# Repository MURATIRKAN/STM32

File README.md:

YAZILIM GELİŞTİRME ORTAMI STMCUBE IDE VEYA KEIL ARM : 2021-2024 
STM32 ARM GELİŞTİRME KART SERİSİ
MODEL KARTLAR: E-H
TASARIM:
TASARIM PROGRAMI:AUTODESK EAGLE
DIPTRACE FREE VERSİYON.
----------------------------------

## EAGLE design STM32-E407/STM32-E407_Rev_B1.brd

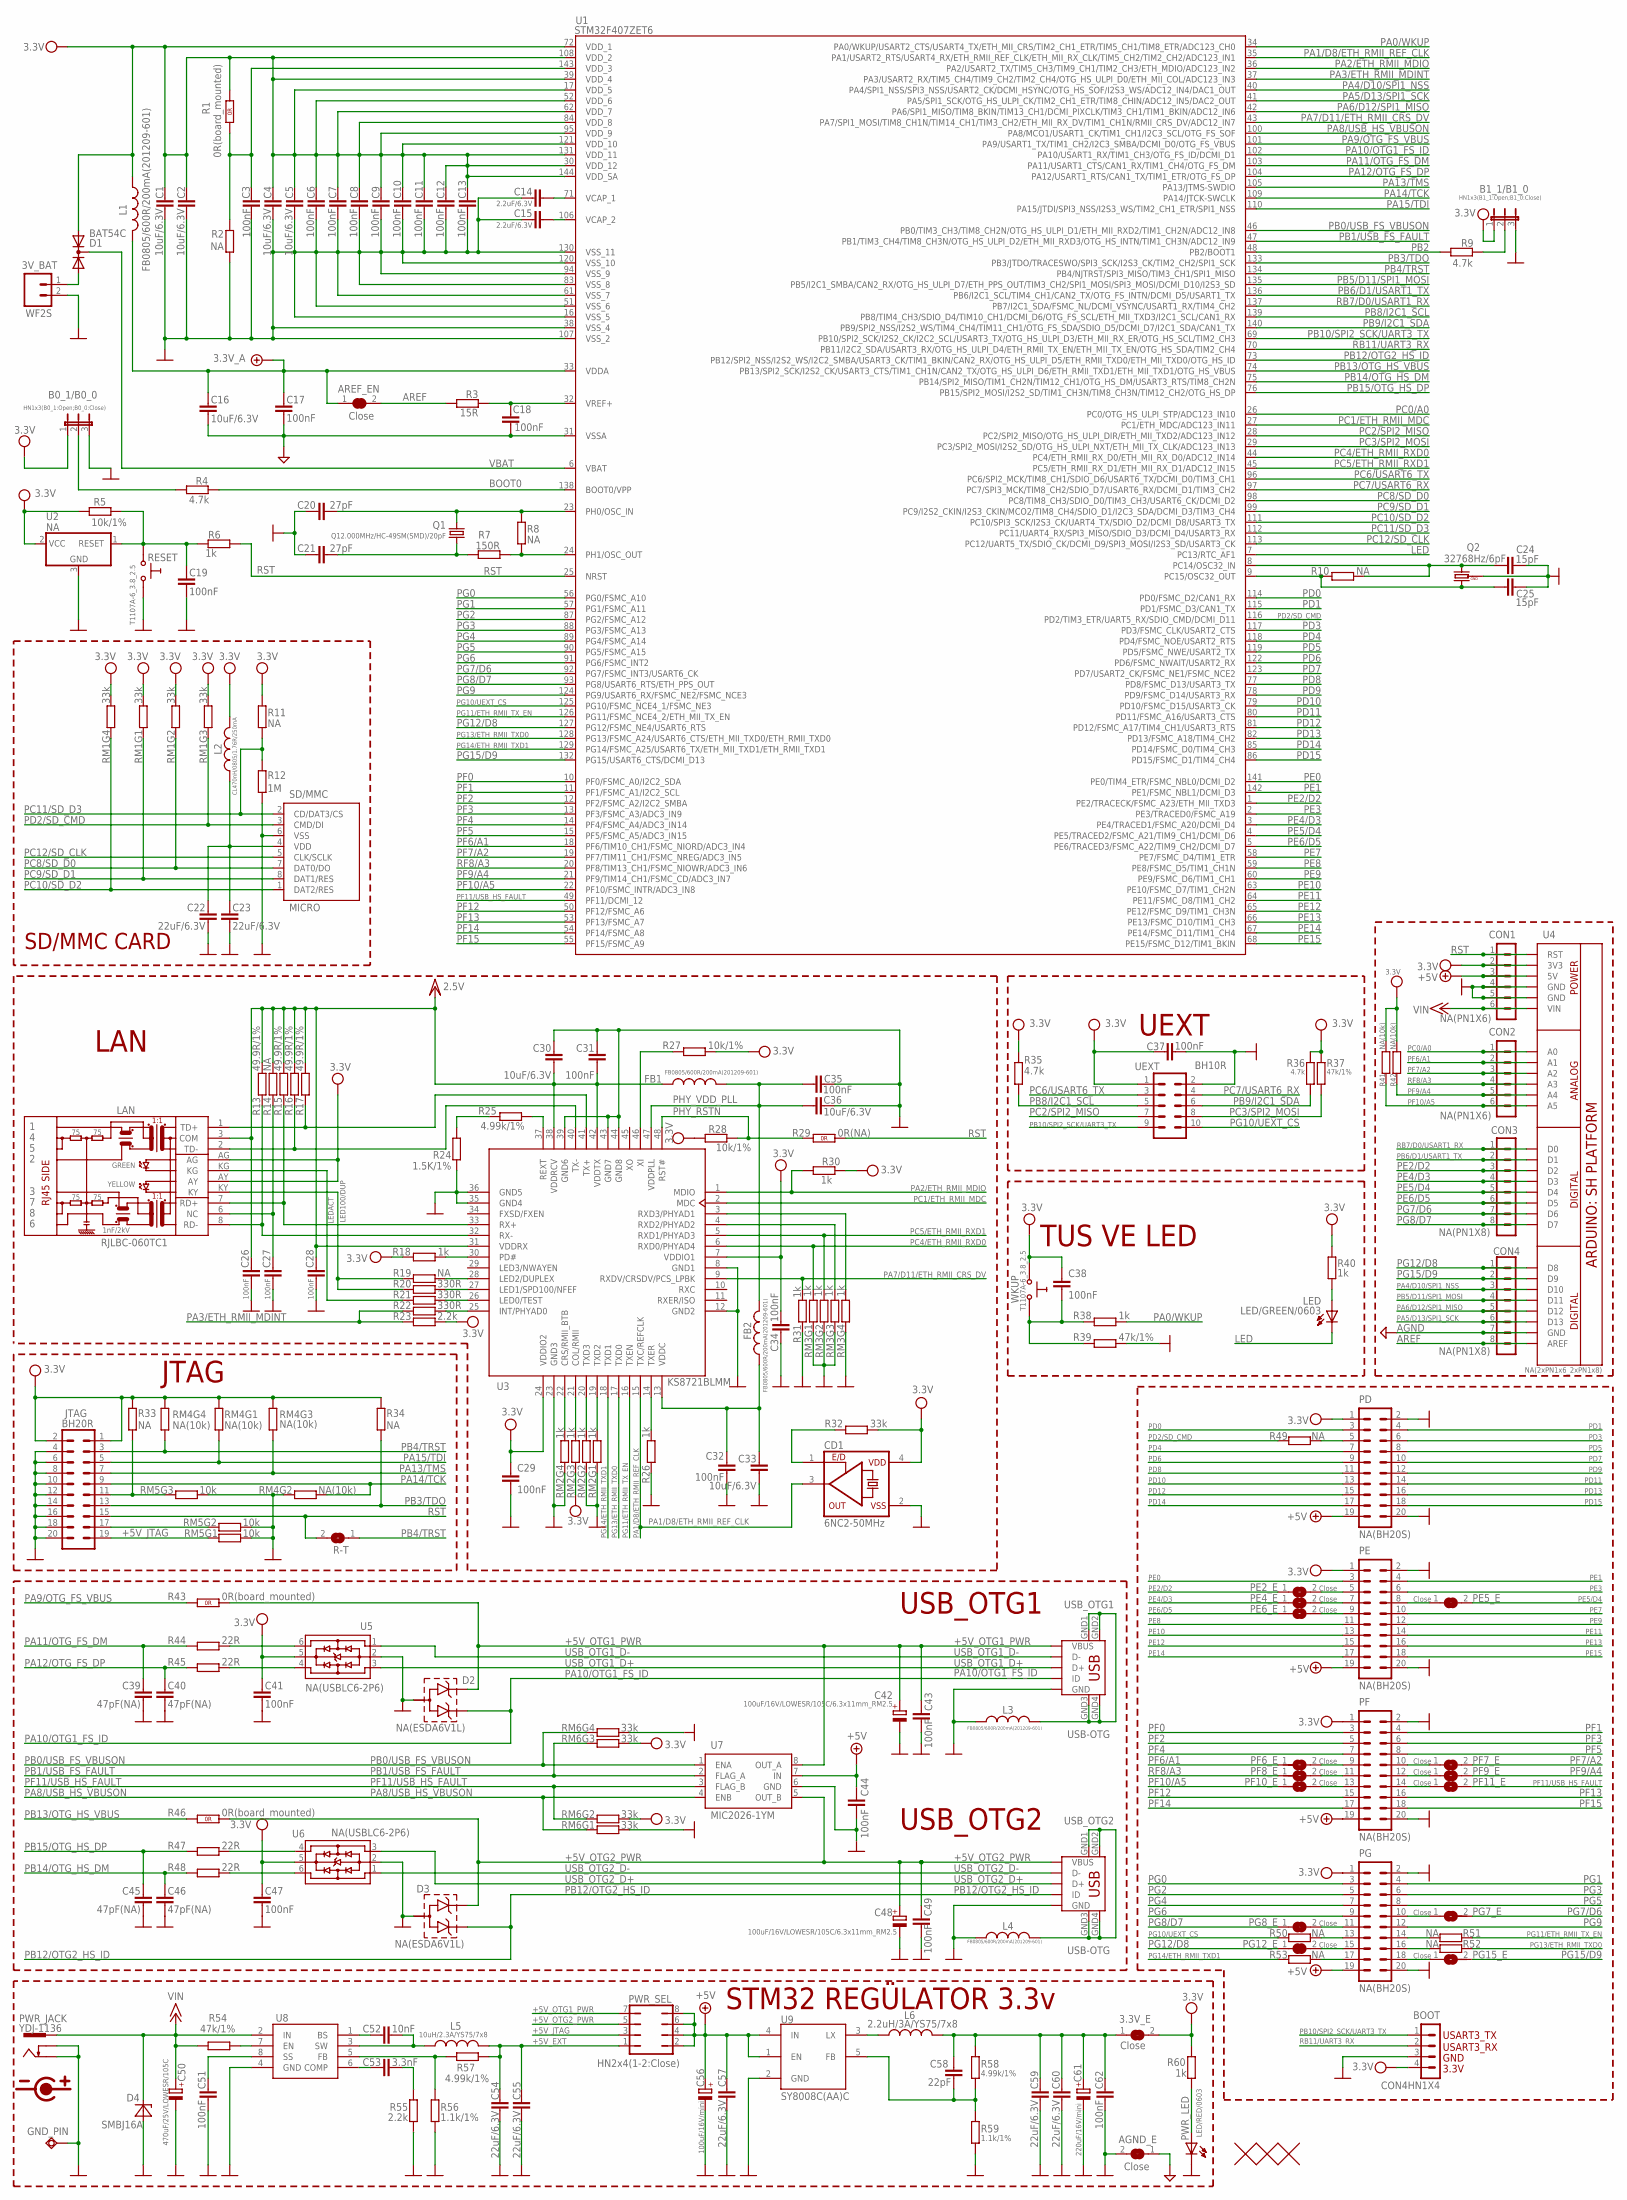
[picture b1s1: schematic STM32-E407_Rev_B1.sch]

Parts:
3.3V_E: Close; SJ_1_SMALLER_CLOSE
3V_BAT: WF2S; CON2.54MM-2-0
AGND_E: Close; SJ_1_SMALLER_CLOSE
AREF_EN: Close; SJ_1_SMALLER_CLOSE
B0_1/B0_0: HN1x3(B0_1:Open;B0_0:Close); JP2
B1_1/B1_0: HN1x3(B1_1:Open;B1_0:Close); JP2
BOOT: CON4HN1X4; HN1X4
C1, C2, C4, C5, C16, C30, C33, C36: 10uF/6.3V; C0603_DWS
C3, C6, C7, C8, C9, C10, C11, C12, C13, C17, C18, C19, C26, C27, C28, C29, C31, C32, C34, C35, C37, C38, C41, C43, C44, C47, C49, C51, C62: 100nF; C0603_DWS
C14, C15: 2.2uF/6.3V; C0603_DWS
C20, C21: 27pF; C0603_DWS
C22, C23, C54, C55, C57, C59, C60: 22uF/6.3V; C0603_DWS
C24, C25: 15pF; C0603_DWS
C39, C40, C45, C46: 47pF(NA); C0603_DWS
C42, C48: 100uF/16V/LOWESR/105C/6.3x11mm_RM2.5; E2,5-6,3
C50: 470uF/25V/LOWESR/105C; E5-10,5
C52: 10nF; C0603_DWS
C53: 3.3nF; C0603_DWS
C56: 100uF/16V/mini; E2,5-6
C58: 22pF; C0603_DWS
C61: 220uF/16V/mini; E3,5-8
CD1: 6NC2-50MHz; 7X5MM_CLOCK_DRIVER
CON1, CON2: NA(PN1X6); PN1X6
CON3, CON4: NA(PN1X8); PN1X8
D1: BAT54C; SOT23C
D2, D3: NA(ESDA6V1L); SOT-23
D4: SMBJ16A; DO214AA
FB1, FB2: FB0805/600R/200mA(201209-601); L0805_5MIL_DWS
GND_PIN: TESTPAD3; TEST_PAD40/70/SQUARE
JTAG: BH20R
L1, L3, L4: FB0805/600R/200mA(201209-601); L0805_5MIL_DWS
L2: CL470nH/0805/1.76R/250mA; L0805_5MIL_DWS
L5: 10uH/2.3A/YS75/7x8; L7078
L6: 2.2uH/3A/YS75/7x8; L7078
LAN: RJLBC-060TC1
LED: LED/GREEN/0603; LED-0603
PD: NA(BH20S); ML20-MALE
PE: NA(BH20S); ML20-MALE
PE2_E, PE4_E, PE5_E, PE6_E: Close; SJ_1_SMALLER_CLOSE
PF: NA(BH20S); ML20-MALE
PF6_E, PF7_E, PF8_E, PF9_E, PF10_E, PF11_E: Close; SJ_1_SMALLER_CLOSE
PG: NA(BH20S); ML20-MALE
PG7_E, PG8_E, PG12_E, PG15_E: Close; SJ_1_SMALLER_CLOSE
PWR_JACK: YDJ-1136; PWR_JACK_UNI_MILLING
PWR_LED: LED/RED/0603; LED-0603
PWR_SEL: HN2x4(1-2:Close); JP4Q_2
Q1: Q12.000MHz/HC-49SM(SMD)/20pF; HC49/SMD2_THIN
Q2: 32768Hz/6pF; TC26H_3_REPAIR_SMD
R1, R43, R46: 0R(board_mounted); 0603_0R
R2, R8, R10, R11, R14, R19, R33, R34: NA; R0603_5MIL_DWS_NA
R3: 15R; R0603_5MIL_DWS
R4, R9, R35, R36: 4.7k; R0603_5MIL_DWS
R5, R27, R28: 10k/1%; R0603_5MIL_DWS
R6, R18, R26, R30, R31, R38, R40, R60: 1k; R0603_5MIL_DWS
R7: 150R; R0603_5MIL_DWS
R12: 1M; R0603_5MIL_DWS
R13, R15, R16, R17: 49.9R/1%; R0603_5MIL_DWS
R20, R21, R22: 330R; R0603_5MIL_DWS
R23, R55: 2.2k; R0603_5MIL_DWS
R24: 1.5K/1%; R0603_5MIL_DWS
R25, R57, R58: 4.99k/1%; R0603_5MIL_DWS
R29: 0R(NA); 0603_0R
R32: 33k; R0603_5MIL_DWS
R37, R39, R54: 47k/1%; R0603_5MIL_DWS
R41, R42: NA(10k); R0603_5MIL_DWS_NA
R44, R45, R47, R48: 22R; R0603_5MIL_DWS
R49, R50, R51, R52, R53: NA; R0603_5MIL_DWS
R56, R59: 1.1k/1%; R0603_5MIL_DWS
R-T: Open; SJ_1_SMALLER
RESET: T1107A-6_3.8_2.5; SW-TAKT_6X3.5_SMD
RM1, RM6: 33k; R_MATRIX_4
RM2, RM3: 1k; R_MATRIX_4
RM4: NA(10k); R_MATRIX_4
RM5: 10k; R_MATRIX_4
SD/MMC: MICRO; TFR-MEM-CON
U1: STM32F407ZET6; LQFP144
U2: NA; SOT23
U3: KS8721BLMM; LQFP48_MM
U4: NA(2xPN1x6_2xPN1x8); ARDUINO_SHIELD_PLATFORM_WITHOUT_DIMENSION
U5, U6: NA(USBLC6-2P6); USBLC6-2P6
U7: MIC2026-1YM; SO-8
U8: MP1482DS; SOIC8
U9: SY8008C(AA)C; SOT23-5
U$1, U$2, U$9: FIDUCIAL1X2; FIDUCIAL-1X2
UEXT: BH10R
USB_OTG1, USB_OTG2: USB-OTG; USB_MINI_9PIN
WKUP: T1107A-6_3.8_2.5; SW-TAKT_6X3.5_SMD

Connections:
+5V: C44.1, C56.+, C57.1, CON1.3, PD.19, PE.19, PF.19, PG.19, PWR_SEL.2, PWR_SEL.4, PWR_SEL.6, PWR_SEL.8, U4.5V, U7.7 (IN), U9.1 (EN), U9.4 (IN)
+5V_EXT: C54.1, C55.1, L5.2, PWR_SEL.1, R57.2
+5V_JTAG: JTAG.19, PWR_SEL.3, RM5.1.1 (1)
+5V_OTG1_PWR: C42.+, C43.1, D2.1, PWR_SEL.7, R43.2 (1.2), U7.8 (OUT_A), USB_OTG1.VBUS
+5V_OTG2_PWR: C48.+, C49.1, D3.1, PWR_SEL.5, R46.2 (1.2), U7.5 (OUT_B), USB_OTG2.VBUS
+7V: AREF_EN.1, C16.1, C17.2, L1.2, U1.33 (VDDA)
+15V: C50.+, CON1.6, D4.C, PWR_JACK.+, R54.1, U4.VIN, U8.2 (IN)
AGND: AGND_E.1, C16.2, C17.1, C18.1, CON4.7, U1.31 (VSSA), U4.GND@2 (GND)
AREF: AREF_EN.2, CON4.8, R3.1, U4.AREF
BOOT0: R4.1, U1.138 (BOOT0/VPP)
GND: 3V_BAT.2, AGND_E.2, B0_1/B0_0.3, B1_1/B1_0.3, BOOT.3, C1.1, C2.1, C3.1, C4.1, C5.1, C6.1, C7.1, C8.1, C9.1, C10.1, C11.1, C12.1, C13.1, C14.1, C15.1, C19.1, C20.2, C21.2, C22.2, C23.2, C24.2, C25.2, C26.2, C27.1, C28.2, C29.2, C30.1, C31.1, C32.2, C33.2, C34.2, C35.2, C36.2, C37.1, C39.2, C40.2, C41.1, C42.-, C43.2, C44.2, C45.2, C46.2, C47.1, C48.-, C49.2, C50.-, C51.2, C54.2, C55.2, C56.-, C57.2, C59.2, C60.2, C61.-, C62.2, CD1.2 (VSS), CON1.4, CON1.5, D2.3, D3.3, D4.A, GND_PIN.P$1, JTAG.4, JTAG.6, JTAG.8, JTAG.10, JTAG.12, JTAG.14, JTAG.16, JTAG.18, JTAG.20, L3.1, L4.1, PD.2, PD.20, PE.2, PE.20, PF.2, PF.20, PG.2, PG.20, PWR_JACK.-, PWR_JACK.--, PWR_LED.C, Q2.GND, R2.2, R12.2, R24.2, R26.2, R31.2, R39.1, R55.2, R56.2, R59.2, RESET.P$2 (1), RM2.1.1 (1), RM2.2.1 (1), RM2.4.1 (1), RM3.1.2 (2), RM3.2.2 (2), RM3.3.2 (2), RM3.4.2 (2), RM4.2.1 (1), RM5.1.2 (2), RM5.2.2 (2), RM5.3.2 (2), RM6.1.2 (2), RM6.4.2 (2), SD/MMC.6 (VSS), U1.16 (VSS_5), U1.38 (VSS_4), U1.51 (VSS_6), U1.61 (VSS_7), U1.83 (VSS_8), U1.94 (VSS_9), U1.107 (VSS_2), U1.120 (VSS_10), U1.130 (VSS_11), U2.3 (GND), U3.8 (GND1), U3.12 (GND2), U3.23 (GND3), U3.35 (GND4), U3.36 (GND5), U3.39 (GND6), U3.43 (GND7), U3.44 (GND8), U4.GND, U4.GND@1 (GND), U5.2, U6.2, U7.6 (GND), U8.4 (GND), U9.2 (GND), UEXT.2, USB_OTG1.GND, USB_OTG2.GND
LED: LED.C, U1.7 (PC13/RTC_AF1)
LED100/DUP: LAN.KY, R19.1, R20.1
LEDACT: LAN.KG, R21.1
unnamed: C20.1, Q1.2, R8.2, U1.23 (PH0/OSC_IN)
unnamed: C21.1, Q1.1, R7.1
unnamed: R7.2, R8.1, U1.24 (PH1/OSC_OUT)
unnamed: JTAG.17, RM5.2.1 (1)
unnamed: LED.A, R40.1
unnamed: PD.5, R49.1
unnamed: R24.1, R25.1
unnamed: C58.2, R58.2, R59.1, U9.5 (FB)
unnamed: B0_1/B0_0.2, R4.2
unnamed: 3.3V_E.1, C58.1, C59.1, C60.1, C61.+, C62.1, L6.2, R58.1
unnamed: C32.1, C33.1, FB2.2, U3.13 (VDDC)
unnamed: PG.14, R51.2
unnamed: PF.13, PF10_E.2
unnamed: PG.16, R52.2
unnamed: PF.9, PF6_E.2
unnamed: PF.11, PF8_E.2
unnamed: PF.10, PF7_E.1
unnamed: PG.17, R53.1
unnamed: PF.12, PF9_E.1
unnamed: LAN.2 (TD-), R16.1, U3.40 (TX-)
unnamed: LAN.1 (TD+), R17.1, U3.41 (TX+)
unnamed: R26.1, U3.14 (TXER)
unnamed: PG.10, PG7_E.1
unnamed: C38.1, R38.1, R39.2, WKUP.P$2 (1)
unnamed: PE.8, PE5_E.1
unnamed: PE.9, PE6_E.2
unnamed: PE.7, PE4_E.2
unnamed: B1_1/B1_0.2, R9.2
unnamed: PE.5, PE2_E.2
unnamed: PG.11, PG8_E.2
unnamed: LAN.7 (RD+), R15.1, U3.33 (RX+)
unnamed: PG.15, PG12_E.2
unnamed: PG.18, PG15_E.1
unnamed: C51.1, U8.8 (SS)
unnamed: R54.2, U8.7 (EN)
unnamed: PG.13, R50.1
unnamed: PF.14, PF11_E.1
unnamed: R20.2, U3.27 (LED1/SPD100/NFEF)
unnamed: R47.2, U6.4
unnamed: R21.2, U3.26 (LED0/TEST)
unnamed: C52.1, U8.1 (BS)
unnamed: R48.2, U6.6
unnamed: R18.2, U3.30 (PD#)
unnamed: C52.2, L5.1, U8.3 (SW)
unnamed: R44.2, U5.6
unnamed: R45.2, U5.4
unnamed: C53.1, U8.6 (COMP)
unnamed: C53.2, R55.1
unnamed: R56.1, R57.1, U8.5 (FB)
unnamed: L6.1, U9.3 (LX)
unnamed: R19.2, U3.28 (LED2/DUPLEX)
unnamed: R25.2, U3.37 (REXT)
unnamed: 3V_BAT.1, D1.2 (A2)
unnamed: C22.1, C23.1, L2.2, SD/MMC.4 (VDD)
unnamed: C27.2, LAN.6 (NC), R14.1
unnamed: LAN.8 (RD-), R13.1, U3.32 (RX-)
unnamed: JTAG.11, R33.1, RM5.3.1 (1)
unnamed: RM2.3.2 (2), U3.21 (COL/RMII)
unnamed: RM2.4.2 (2), U3.22 (CRS/RMII_BTB)
unnamed: RM3.3.1 (1), U3.4 (RXD2/PHYAD2)
unnamed: RM3.4.1 (1), U3.3 (RXD3/PHYAD1)
unnamed: C14.2, U1.71 (VCAP_1)
unnamed: CD1.1 (E/D), R32.2
unnamed: R22.2, U3.25 (INT/PHYAD0)
unnamed: R27.2, U3.46 (XI)
unnamed: RM2.1.2 (2), U3.19 (TXD2)
unnamed: RM2.2.2 (2), U3.20 (TXD3)
unnamed: C15.2, U1.106 (VCAP_2)
unnamed: PWR_LED.A, R60.2
unnamed: C19.2, R5.1, R6.2, RESET.P$1 (0), U2.1 (RESET)
unnamed: C3.2, R1.1 (1.1), R2.1, U1.143 (VDD_3)
PA0/WKUP: R38.2, U1.34 (PA0/WKUP/USART2_CTS/USART4_TX/ETH_MII_C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)
PA1/D8/ETH_RMII_REF_CLK: CD1.3 (OUT), U1.35 (PA1/USART2_RTS/USART4_RX/ETH_RMII_REF_C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), U3.15 (TXC/REFCLK)
PA2/ETH_RMII_MDIO: R30.2, U1.36 (PA2/USART2_TX/TIM5_CH3/TIM9_CH1/TIM2_CH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), U3.1 (MDIO)
PA3/ETH_RMII_MDINT: R22.1, R23.1, U1.37 (PA3/USART2_RX/TIM5_CH4/TIM9_CH2/TIM2_CH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)
PA4/D10/SPI1_NSS: CON4.3, U1.40 (PA4/SPI1_NSS/SPI3_NSS/USART2_CK/DCMI_HS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), U4.D10
PA5/D13/SPI1_SCK: CON4.6, U1.41 (PA5/SPI1_SCK/OTG_HS_ULPI_CK/TIM2_CH1_ET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), U4.D13
PA6/D12/SPI1_MISO: CON4.5, U1.42 (PA6/SPI1_MISO/TIM8_BKIN/TIM13_CH1/DCMI_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), U4.D12
PA7/D11/ETH_RMII_CRS_DV: R31.1, U1.43 (PA7/SPI1_MOSI/TIM8_CH1N/TIM14_CH1/TIM3_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), U3.9 (RXDV/CRSDV/PCS_LPBK)
PA8/USB_HS_VBUSON: RM6.1.1 (1), U1.100 (PA8/MCO1/USART1_CK/TIM1_CH1/I2C3_SCL/OT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), U7.4 (ENB)
PA9/OTG_FS_VBUS: R43.1 (1.1), U1.101 (PA9/USART1_TX/TIM1_CH2/I2C3_SMBA/DCMI_D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)
PA10/OTG1_FS_ID: D2.2, U1.102 (PA10/USART1_RX/TIM1_CH3/OTG_FS_ID/DCMI_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), USB_OTG1.ID
PA11/OTG_FS_DM: C39.1, R44.1, U1.103 (PA11/USART1_CTS/CAN1_RX/TIM1_CH4/OTG_FS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)
PA12/OTG_FS_DP: C40.1, R45.1, U1.104 (PA12/USART1_RTS/CAN1_TX/TIM1_ETR/OTG_FS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)
PA13/TMS: JTAG.7, RM4.3.1 (1), U1.105 (PA13/JTMS-SWDIO)
PA14/TCK: JTAG.9, RM4.2.2 (2), U1.109 (PA14/JTCK-SWCLK)
PA15/TDI: JTAG.5, RM4.1.1 (1), U1.110 (PA15/JTDI/SPI3_NSS/I2S3_WS/TIM2_CH1_ETR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)
PB0/USB_FS_VBUSON: RM6.4.1 (1), U1.46 (PB0/TIM3_CH3/TIM8_CH2N/OTG_HS_ULPI_D1/E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), U7.1 (ENA)
PB1/USB_FS_FAULT: RM6.3.1 (1), U1.47 (PB1/TIM3_CH4/TIM8_CH3N/OTG_HS_ULPI_D2/E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), U7.2 (FLAG_A)
PB2: R9.1, U1.48 (PB2/BOOT1)
PB3/TDO: JTAG.13, R34.1, U1.133 (PB3/JTDO/TRACESWO/SPI3_SCK/I2S3_CK/TIM2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)
PB4/TRST: JTAG.3, R-T.1, RM4.4.1 (1), U1.134 (PB4/NJTRST/SPI3_MISO/TIM3_CH1/SPI1_MISO)
PB5/D11/SPI1_MOSI: CON4.4, U1.135 (PB5/I2C1_SMBA/CAN2_RX/OTG_HS_ULPI_D7/ET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), U4.D11
PB6/D1/USART1_TX: CON3.2, U1.136 (PB6/I2C1_SCL/TIM4_CH1/CAN2_TX/OTG_FS_IN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), U4.D1
PB8/I2C1_SCL: R35.1, U1.139 (PB8/TIM4_CH3/SDIO_D4/TIM10_CH1/DCMI_D6/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), UEXT.5
PB9/I2C1_SDA: R36.1, U1.140 (PB9/SPI2_NSS/I2S2_WS/TIM4_CH4/TIM11_CH1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), UEXT.6
PB10/SPI2_SCK/UART3_TX: BOOT.1, U1.69 (PB10/SPI2_SCK/I2S2_CK/I2C2_SCL/USART3_T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), UEXT.9
PB12/OTG2_HS_ID: D3.2, U1.73 (PB12/SPI2_NSS/I2S2_WS/I2C2_SMBA/USART3_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), USB_OTG2.ID
PB13/OTG_HS_VBUS: R46.1 (1.1), U1.74 (PB13/SPI2_SCK/I2S2_CK/USART3_CTS/TIM1_C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)
PB14/OTG_HS_DM: C46.1, R48.1, U1.75 (PB14/SPI2_MISO/TIM1_CH2N/TIM12_CH1/OTG_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)
PB15/OTG_HS_DP: C45.1, R47.1, U1.76 (PB15/SPI2_MOSI/I2S2_SD/TIM1_CH3N/TIM8_C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)
PC0/A0: CON2.1, U1.26 (PC0/OTG_HS_ULPI_STP/ADC123_IN10), U4.A0
PC1/ETH_RMII_MDC: U1.27 (PC1/ETH_MDC/ADC123_IN11), U3.2 (MDC)
PC2/SPI2_MISO: U1.28 (PC2/SPI2_MISO/OTG_HS_ULPI_DIR/ETH_MII_T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), UEXT.7
PC3/SPI2_MOSI: R37.1, U1.29 (PC3/SPI2_MOSI/I2S2_SD/OTG_HS_ULPI_NXT/E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), UEXT.8
PC4/ETH_RMII_RXD0: RM3.1.1 (1), U1.44 (PC4/ETH_RMII_RX_D0/ETH_MII_RX_D0/ADC12_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), U3.6 (RXD0/PHYAD4)
PC5/ETH_RMII_RXD1: RM3.2.1 (1), U1.45 (PC5/ETH_RMII_RX_D1/ETH_MII_RX_D1/ADC12_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), U3.5 (RXD1/PHYAD3)
PC6/USART6_TX: U1.96 (PC6/SPI2_MCK/TIM8_CH1/SDIO_D6/USART6_TX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), UEXT.3
PC7/USART6_RX: U1.97 (PC7/SPI3_MCK/TIM8_CH2/SDIO_D7/USART6_RX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), UEXT.4
PC8/SD_D0: RM1.2.1 (1), SD/MMC.7 (DAT0/DO), U1.98 (PC8/TIM8_CH3/SDIO_D0/TIM3_CH3/USART6_CK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)
PC9/SD_D1: RM1.1.1 (1), SD/MMC.8 (DAT1/RES), U1.99 (PC9/I2S2_CKIN/I2S3_CKIN/MCO2/TIM8_CH4/S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)
PC10/SD_D2: RM1.4.1 (1), SD/MMC.1 (DAT2/RES), U1.111 (PC10/SPI3_SCK/I2S3_CK/UART4_TX/SDIO_D2/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)
PC11/SD_D3: R11.2, R12.1, SD/MMC.2 (CD/DAT3/CS), U1.112 (PC11/UART4_RX/SPI3_MISO/SDIO_D3/DCMI_D4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)
PC12/SD_CLK: SD/MMC.5 (CLK/SCLK), U1.113 (PC12/UART5_TX/SDIO_CK/DCMI_D9/SPI3_MOSI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)
PC14: C24.1, Q2.2, R10.2, U1.8 (PC14/OSC32_IN)
PC15: C25.1, Q2.1, R10.1, U1.9 (PC15/OSC32_OUT)
PD0: PD.3, U1.114 (PD0/FSMC_D2/CAN1_RX)
PD1: PD.4, U1.115 (PD1/FSMC_D3/CAN1_TX)
PD2/SD_CMD: R49.2, RM1.3.1 (1), SD/MMC.3 (CMD/DI), U1.116 (PD2/TIM3_ETR/UART5_RX/SDIO_CMD/DCMI_D11)
PD3: PD.6, U1.117 (PD3/FSMC_CLK/USART2_CTS)
PD4: PD.7, U1.118 (PD4/FSMC_NOE/USART2_RTS)
PD5: PD.8, U1.119 (PD5/FSMC_NWE/USART2_TX)
PD6: PD.9, U1.122 (PD6/FSMC_NWAIT/USART2_RX)
PD7: PD.10, U1.123 (PD7/USART2_CK/FSMC_NE1/FSMC_NCE2)
PD8: PD.11, U1.77 (PD8/FSMC_D13/USART3_TX)
PD9: PD.12, U1.78 (PD9/FSMC_D14/USART3_RX)
PD10: PD.13, U1.79 (PD10/FSMC_D15/USART3_CK)
PD11: PD.14, U1.80 (PD11/FSMC_A16/USART3_CTS)
PD12: PD.15, U1.81 (PD12/FSMC_A17/TIM4_CH1/USART3_RTS)
PD13: PD.16, U1.82 (PD13/FSMC_A18/TIM4_CH2)
PD14: PD.17, U1.85 (PD14/FSMC_D0/TIM4_CH3)
PD15: PD.18, U1.86 (PD15/FSMC_D1/TIM4_CH4)
PE0: PE.3, U1.141 (PE0/TIM4_ETR/FSMC_NBL0/DCMI_D2)
PE1: PE.4, U1.142 (PE1/FSMC_NBL1/DCMI_D3)
PE2/D2: CON3.3, PE2_E.1, U1.1 (PE2/TRACECK/FSMC_A23/ETH_MII_TXD3), U4.D2
PE3: PE.6, U1.2 (PE3/TRACED0/FSMC_A19)
PE4/D3: CON3.4, PE4_E.1, U1.3 (PE4/TRACED1/FSMC_A20/DCMI_D4), U4.D3
PE5/D4: CON3.5, PE5_E.2, U1.4 (PE5/TRACED2/FSMC_A21/TIM9_CH1/DCMI_D6), U4.D4
PE6/D5: CON3.6, PE6_E.1, U1.5 (PE6/TRACED3/FSMC_A22/TIM9_CH2/DCMI_D7), U4.D5
PE7: PE.10, U1.58 (PE7/FSMC_D4/TIM1_ETR)
PE8: PE.11, U1.59 (PE8/FSMC_D5/TIM1_CH1N)
PE9: PE.12, U1.60 (PE9/FSMC_D6/TIM1_CH1)
PE10: PE.13, U1.63 (PE10/FSMC_D7/TIM1_CH2N)
PE11: PE.14, U1.64 (PE11/FSMC_D8/TIM1_CH2)
PE12: PE.15, U1.65 (PE12/FSMC_D9/TIM1_CH3N)
PE13: PE.16, U1.66 (PE13/FSMC_D10/TIM1_CH3)
PE14: PE.17, U1.67 (PE14/FSMC_D11/TIM1_CH4)
PE15: PE.18, U1.68 (PE15/FSMC_D12/TIM1_BKIN)
PF0: PF.3, U1.10 (PF0/FSMC_A0/I2C2_SDA)
PF1: PF.4, U1.11 (PF1/FSMC_A1/I2C2_SCL)
PF2: PF.5, U1.12 (PF2/FSMC_A2/I2C2_SMBA)
PF3: PF.6, U1.13 (PF3/FSMC_A3/ADC3_IN9)
PF4: PF.7, U1.14 (PF4/FSMC_A4/ADC3_IN14)
PF5: PF.8, U1.15 (PF5/FSMC_A5/ADC3_IN15)
PF6/A1: CON2.2, PF6_E.1, U1.18 (PF6/TIM10_CH1/FSMC_NIORD/ADC3_IN4), U4.A1
PF7/A2: CON2.3, PF7_E.2, U1.19 (PF7/TIM11_CH1/FSMC_NREG/ADC3_IN5), U4.A2
PF9/A4: CON2.5, PF9_E.2, R42.1, U1.21 (PF9/TIM14_CH1/FSMC_CD/ADC3_IN7), U4.A4
PF10/A5: CON2.6, PF10_E.1, R41.1, U1.22 (PF10/FSMC_INTR/ADC3_IN8), U4.A5
PF11/USB_HS_FAULT: PF11_E.2, RM6.2.1 (1), U1.49 (PF11/DCMI_12), U7.3 (FLAG_B)
PF12: PF.15, U1.50 (PF12/FSMC_A6)
PF13: PF.16, U1.53 (PF13/FSMC_A7)
PF14: PF.17, U1.54 (PF14/FSMC_A8)
PF15: PF.18, U1.55 (PF15/FSMC_A9)
PG0: PG.3, U1.56 (PG0/FSMC_A10)
PG1: PG.4, U1.57 (PG1/FSMC_A11)
PG2: PG.5, U1.87 (PG2/FSMC_A12)
PG3: PG.6, U1.88 (PG3/FSMC_A13)
PG4: PG.7, U1.89 (PG4/FSMC_A14)
PG5: PG.8, U1.90 (PG5/FSMC_A15)
PG6: PG.9, U1.91 (PG6/FSMC_INT2)
PG7/D6: CON3.7, PG7_E.2, U1.92 (PG7/FSMC_INT3/USART6_CK), U4.D6
PG8/D7: CON3.8, PG8_E.1, U1.93 (PG8/USART6_RTS/ETH_PPS_OUT), U4.D7
PG9: PG.12, U1.124 (PG9/USART6_RX/FSMC_NE2/FSMC_NCE3)
PG10/UEXT_CS: R50.2, U1.125 (PG10/FSMC_NCE4_1/FSMC_NE3), UEXT.10
PG11/ETH_RMII_TX_EN: R51.1, U1.126 (PG11/FSMC_NCE4_2/ETH_MII_TX_EN), U3.16 (TXEN)
PG12/D8: CON4.1, PG12_E.1, U1.127 (PG12/FSMC_NE4/USART6_RTS), U4.D8
PG13/ETH_RMII_TXD0: R52.1, U1.128 (PG13/FSMC_A24/USART6_CTS/ETH_MII_TXD0/E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), U3.17 (TXD0)
PG14/ETH_RMII_TXD1: R53.2, U1.129 (PG14/FSMC_A25/USART6_TX/ETH_MII_TXD1/ET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), U3.18 (TXD1)
PG15/D9: CON4.2, PG15_E.2, U1.132 (PG15/USART6_CTS/DCMI_D13), U4.D9
PHY_RSTN: R28.2, R29.1 (1.1), U3.48 (RST#)
PHY_VDD_PLL: C35.1, C36.1, FB1.1, FB2.1, U3.47 (VDDPLL)
RB7/D0/USART1_RX: CON3.1, U1.137 (PB7/I2C1_SDA/FSMC_NL/DCMI_VSYNC/USART1_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), U4.D0
RB11/UART3_RX: BOOT.2, U1.70 (PB11/I2C2_SDA/USART3_RX/OTG_HS_ULPI_D4/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)
RF8/A3: CON2.4, PF8_E.1, U1.20 (PF8/TIM13_CH1/FSMC_NIOWR/ADC3_IN6), U4.A3
RST: CON1.1, JTAG.15, R6.1, R29.2 (1.2), R-T.2, U1.25 (NRST), U4.RST
USB_OTG1_D+: U5.3, USB_OTG1.D+
USB_OTG1_D-: U5.1, USB_OTG1.D-
USB_OTG2_D+: U6.3, USB_OTG2.D+
USB_OTG2_D-: U6.1, USB_OTG2.D-
USB_SHIELD1: L4.2, USB_OTG2.GND1, USB_OTG2.GND2, USB_OTG2.GND3, USB_OTG2.GND4
USB_SHIELD2: L3.2, USB_OTG1.GND1, USB_OTG1.GND2, USB_OTG1.GND3, USB_OTG1.GND4
VBAT: D1.3 (K), U1.6 (VBAT)
VCC: 3.3V_E.2, B0_1/B0_0.1, B1_1/B1_0.1, BOOT.4, C1.2, C2.2, C4.2, C5.2, C6.2, C7.2, C8.2, C9.2, C10.2, C11.2, C12.2, C13.2, C29.1, C34.1, C37.2, C38.2, C41.2, C47.2, CD1.4 (VDD), CON1.2, D1.1 (A1), JTAG.1, JTAG.2, L1.1, L2.1, LAN.AG, LAN.AY, PD.1, PE.1, PF.1, PG.1, R1.2 (1.2), R5.2, R11.1, R18.1, R23.2, R27.1, R28.1, R30.1, R32.1, R33.2, R34.2, R35.2, R36.2, R37.2, R40.2, R41.2, R42.2, R60.1, RM1.1.2 (2), RM1.2.2 (2), RM1.3.2 (2), RM1.4.2 (2), RM2.3.1 (1), RM4.1.2 (2), RM4.3.2 (2), RM4.4.2 (2), RM6.2.2 (2), RM6.3.2 (2), U1.17 (VDD_5), U1.30 (VDD_12), U1.39 (VDD_4), U1.52 (VDD_6), U1.62 (VDD_7), U1.72 (VDD_1), U1.84 (VDD_8), U1.95 (VDD_9), U1.108 (VDD_2), U1.121 (VDD_10), U1.131 (VDD_11), U1.144 (VDD_SA), U2.2 (VCC), U3.7 (VDDIO1), U3.24 (VDDIO2), U4.3V3, U5.5, U6.5, UEXT.1, WKUP.P$1 (0)
VCC/2: C26.1, C28.1, C30.2, C31.2, FB1.2, LAN.3 (COM), R13.2, R14.2, R15.2, R16.2, R17.2, U3.31 (VDDRX), U3.38 (VDDRCV), U3.42 (VDDTX)
VREF+: C18.2, R3.2, U1.32 (VREF+)

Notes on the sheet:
STM32 REGÜLATOR 3.3v
TUS VE LED
JTAG
SD/MMC CARD
USART3_TX
USART3_RX
GND
LAN
UEXT
USB_OTG1
USB_OTG2
3.3V

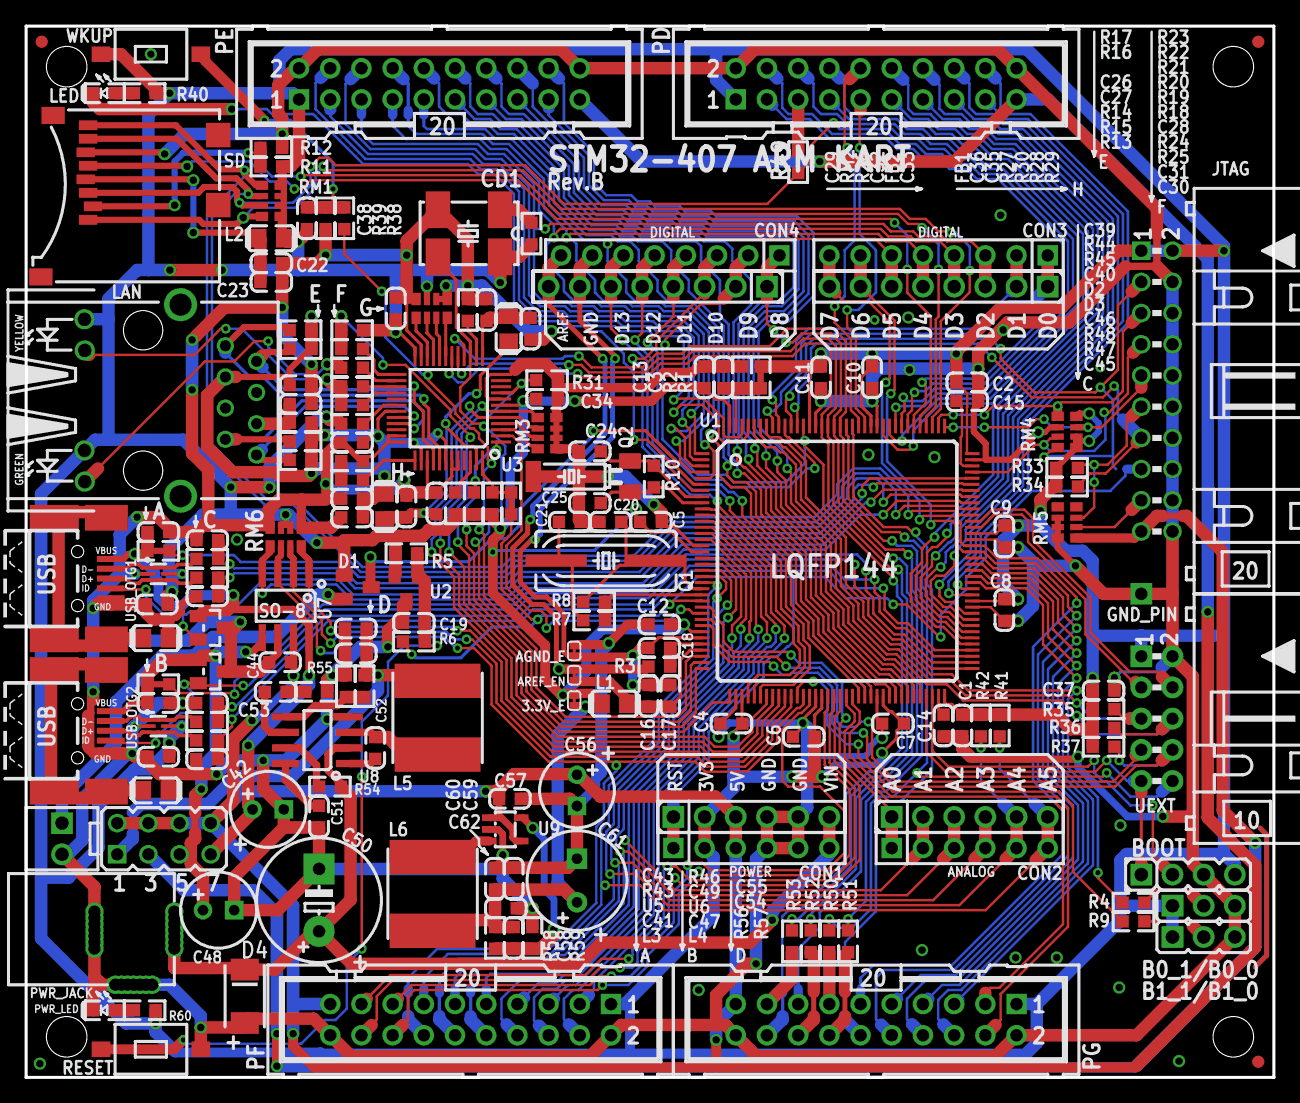
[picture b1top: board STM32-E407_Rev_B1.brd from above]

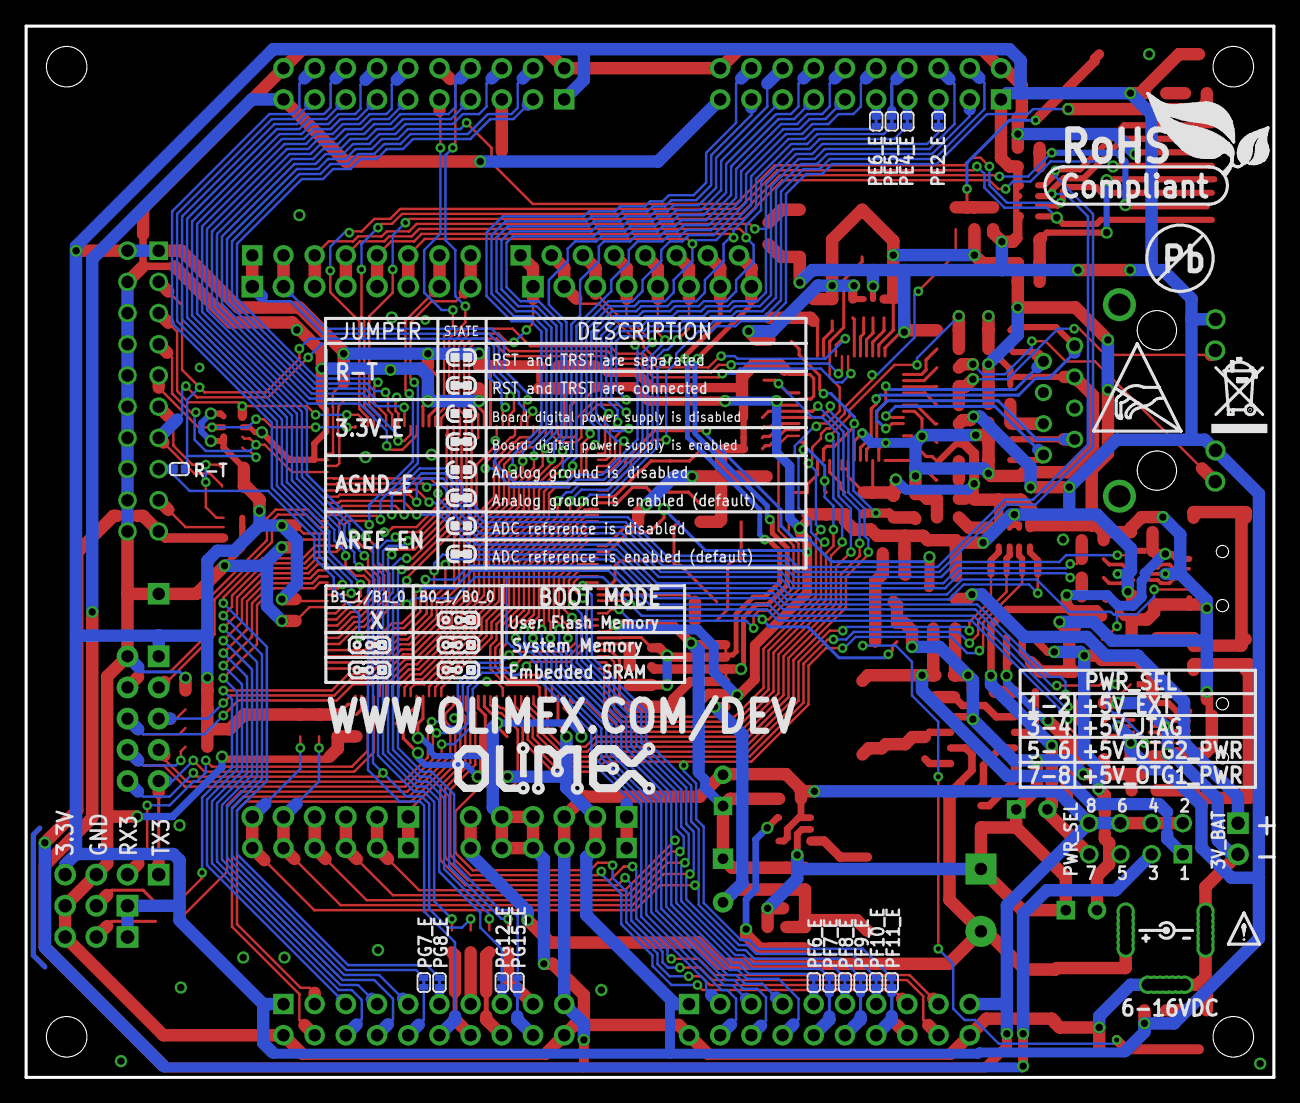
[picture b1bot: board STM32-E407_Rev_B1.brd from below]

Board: 2 copper layers, 101.6 x 85.6 mm, 204 parts (21 on the bottom side), 209 nets.

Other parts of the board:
U$4: OLIMEX1_V
U$5: ESD_SYMBOL
U$6: PB
U$8: RECYCLE_BIN1/8
U$15: ROHS
U$16: ATTENTION_SMALL

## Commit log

2024-06-05 STM32F407-ARM CORTEX M4 DİZAYN
    AUTODESK EAGLE DEVRE + PCB
    ------------------------------------
    ST MICROELECTRONICS
2024-06-05 ST MICROELECTRONICS STM32F407-405 DATASHEET
